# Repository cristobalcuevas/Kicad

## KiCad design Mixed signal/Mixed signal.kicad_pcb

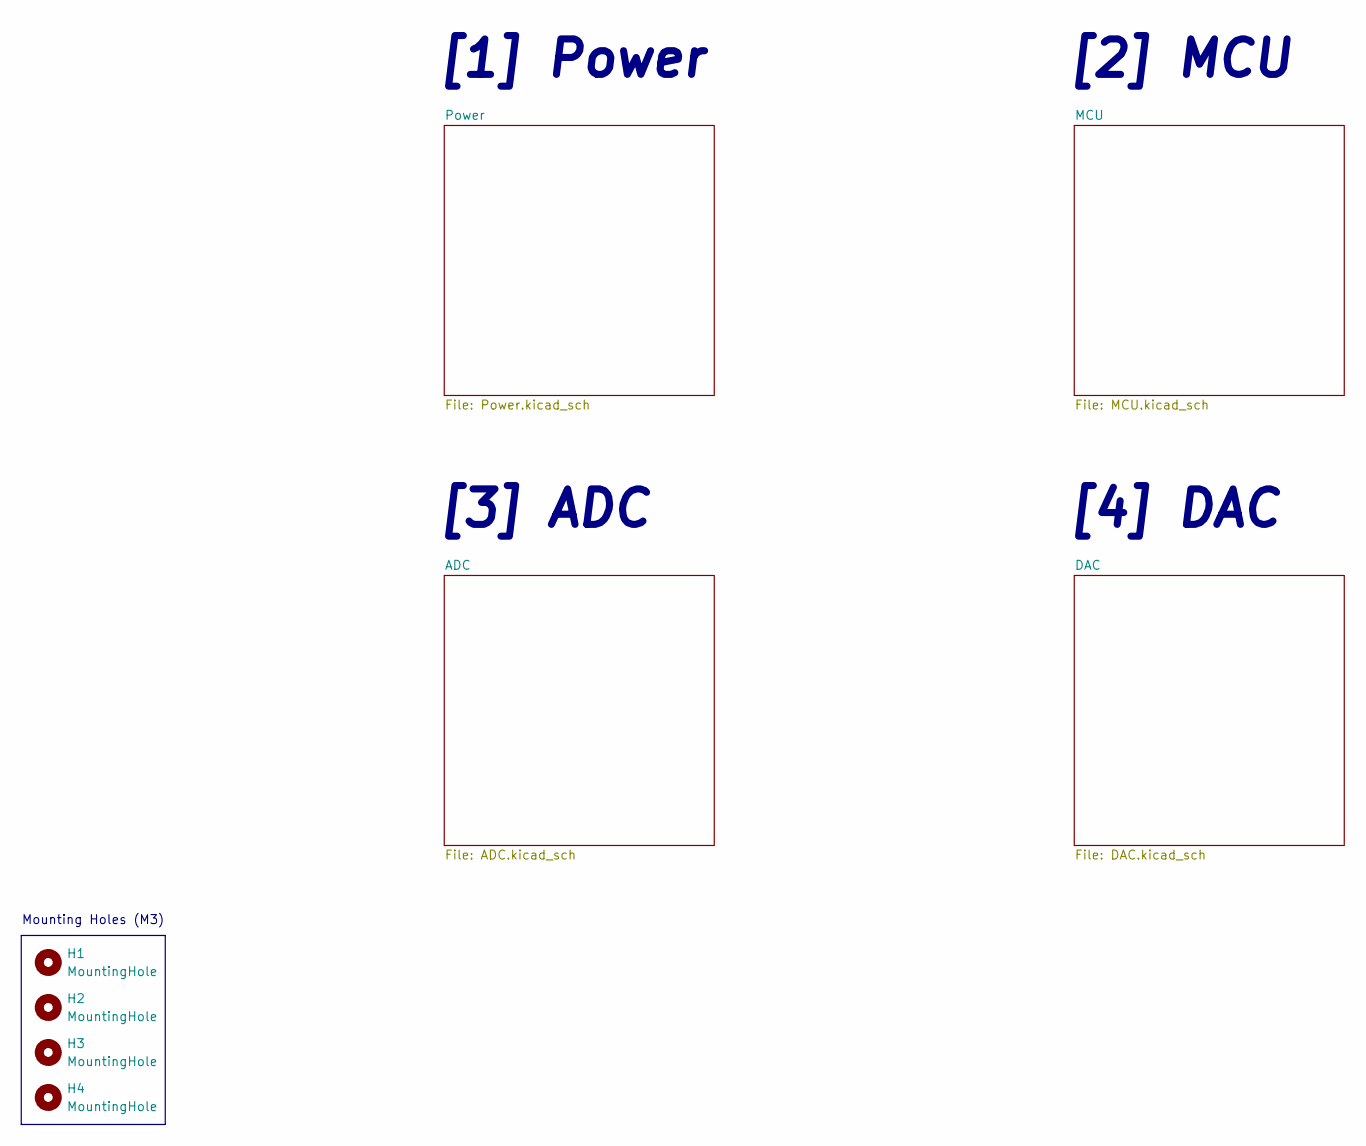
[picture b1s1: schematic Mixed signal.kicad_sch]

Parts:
H1, H2, H3, H4: MountingHole; MountingHole_3.2mm_M3

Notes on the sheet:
[4] DAC
[3] ADC
Mounting Holes (M3)
[2] MCU
[1] Power

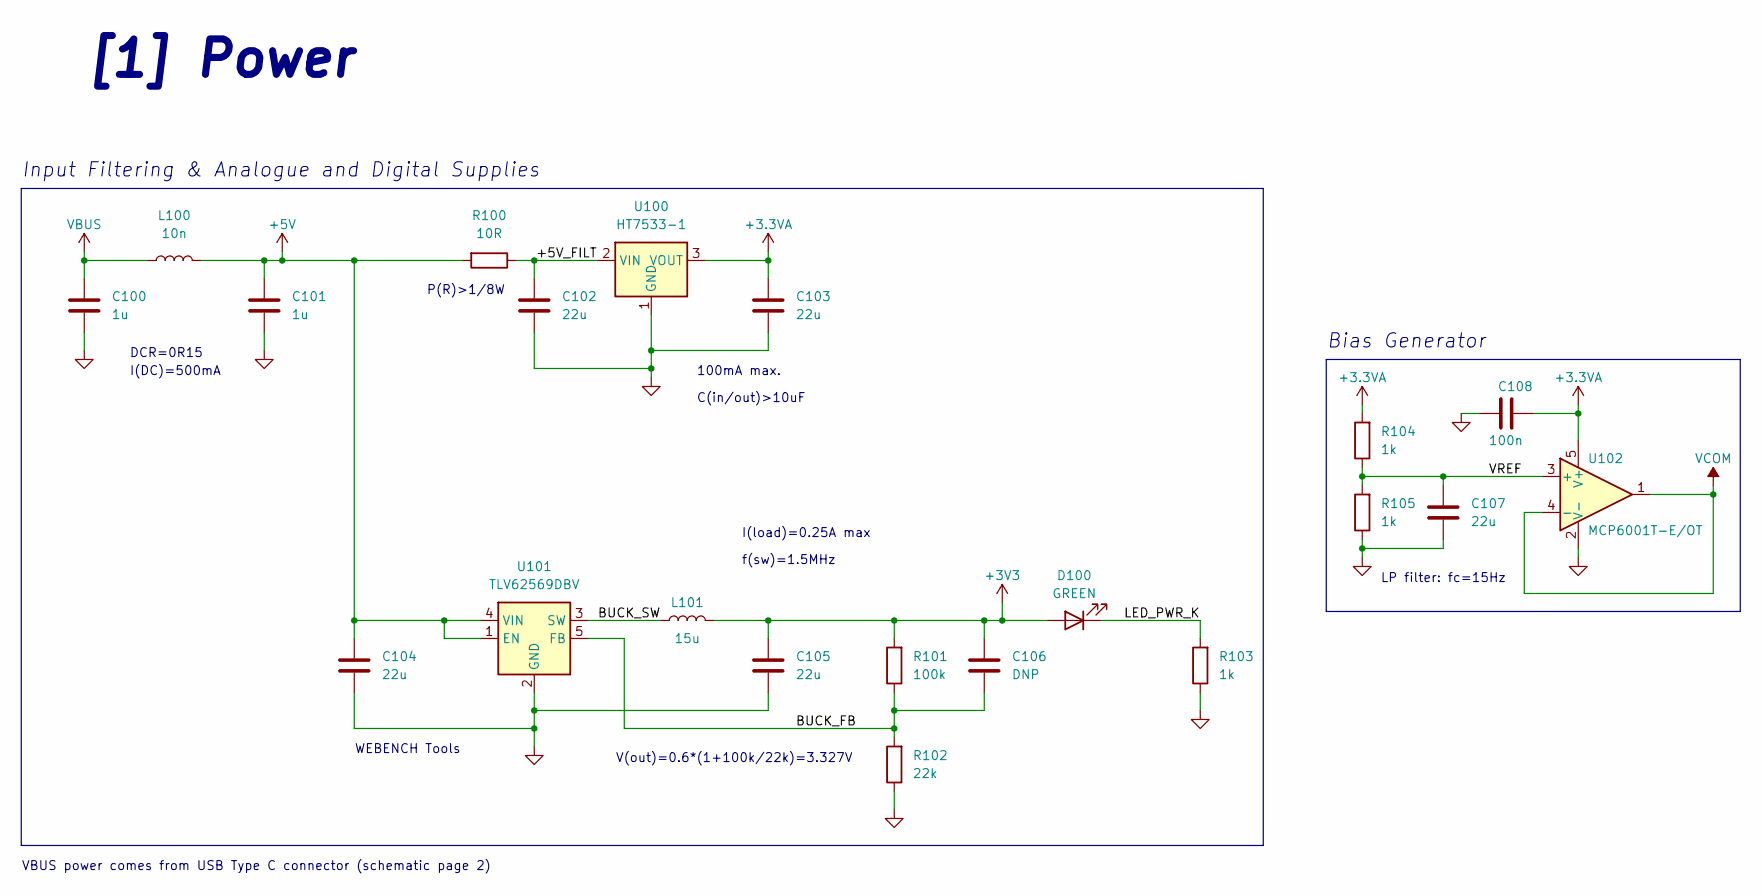
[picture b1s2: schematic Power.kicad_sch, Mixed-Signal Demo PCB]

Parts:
C100, C101: 1u; C_0603_1608Metric
C102, C103, C104, C105, C107: 22u; C_0805_2012Metric
C106: DNP; C_0402_1005Metric
C108: 100n; C_0402_1005Metric
D100: GREEN; LED_0603_1608Metric
L100: 10n; L_0402_1005Metric
L101: 15u; MWSA0603S
R100: 10R; R_0805_2012Metric
R101: 100k; R_0402_1005Metric
R102: 22k; R_0402_1005Metric
R103, R104, R105: 1k; R_0402_1005Metric
U100: HT7533-1; SOT-89-3
U101: TLV62569DBV; SOT-23-5
U102: MCP6001T-E/OT; SOT-23-5

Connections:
+3.3VA: C103.1, C108.1, R104.2, U100.3 (VOUT), U102.5 (V+); also elsewhere on the board
+3V3: C105.1, C106.1, D100.2 (A), L101.2, R101.2; also elsewhere on the board
+5V: C101.1, C104.1, L100.2, R100.2, U101.1 (EN), U101.4 (VIN); also elsewhere on the board
/Power/+5V_FILT: C102.1, R100.1, U100.2 (VIN)
/Power/BUCK_FB: C106.2, R101.1, R102.2, U101.5 (FB)
/Power/BUCK_SW: L101.1, U101.3 (SW)
/Power/LED_PWR_K: D100.1 (K), R103.2
/Power/VREF: C107.1, R104.1, R105.2, U102.3 (+)
GND: C100.2, C101.2, C102.2, C103.2, C104.2, C105.2, C107.2, C108.2, R102.1, R103.1, R105.1, U100.1 (GND), U101.2 (GND), U102.2 (V-); also elsewhere on the board
VBUS: C100.1, L100.1; also elsewhere on the board
VCOM: U102.1, U102.4 (-); also elsewhere on the board

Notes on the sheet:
DCR=0R15
C(in/out)>10uF
V(out)=0.6*(1+100k/22k)=3.327V
I(DC)=500mA
Bias Generator
LP filter: fc=15Hz
100mA max.
f(sw)=1.5MHz
VBUS power comes from USB Type C connector (schematic page 2)
P(R)>1/8W
I(load)=0.25A max
Input Filtering & Analogue and Digital Supplies
[1] Power
WEBENCH Tools

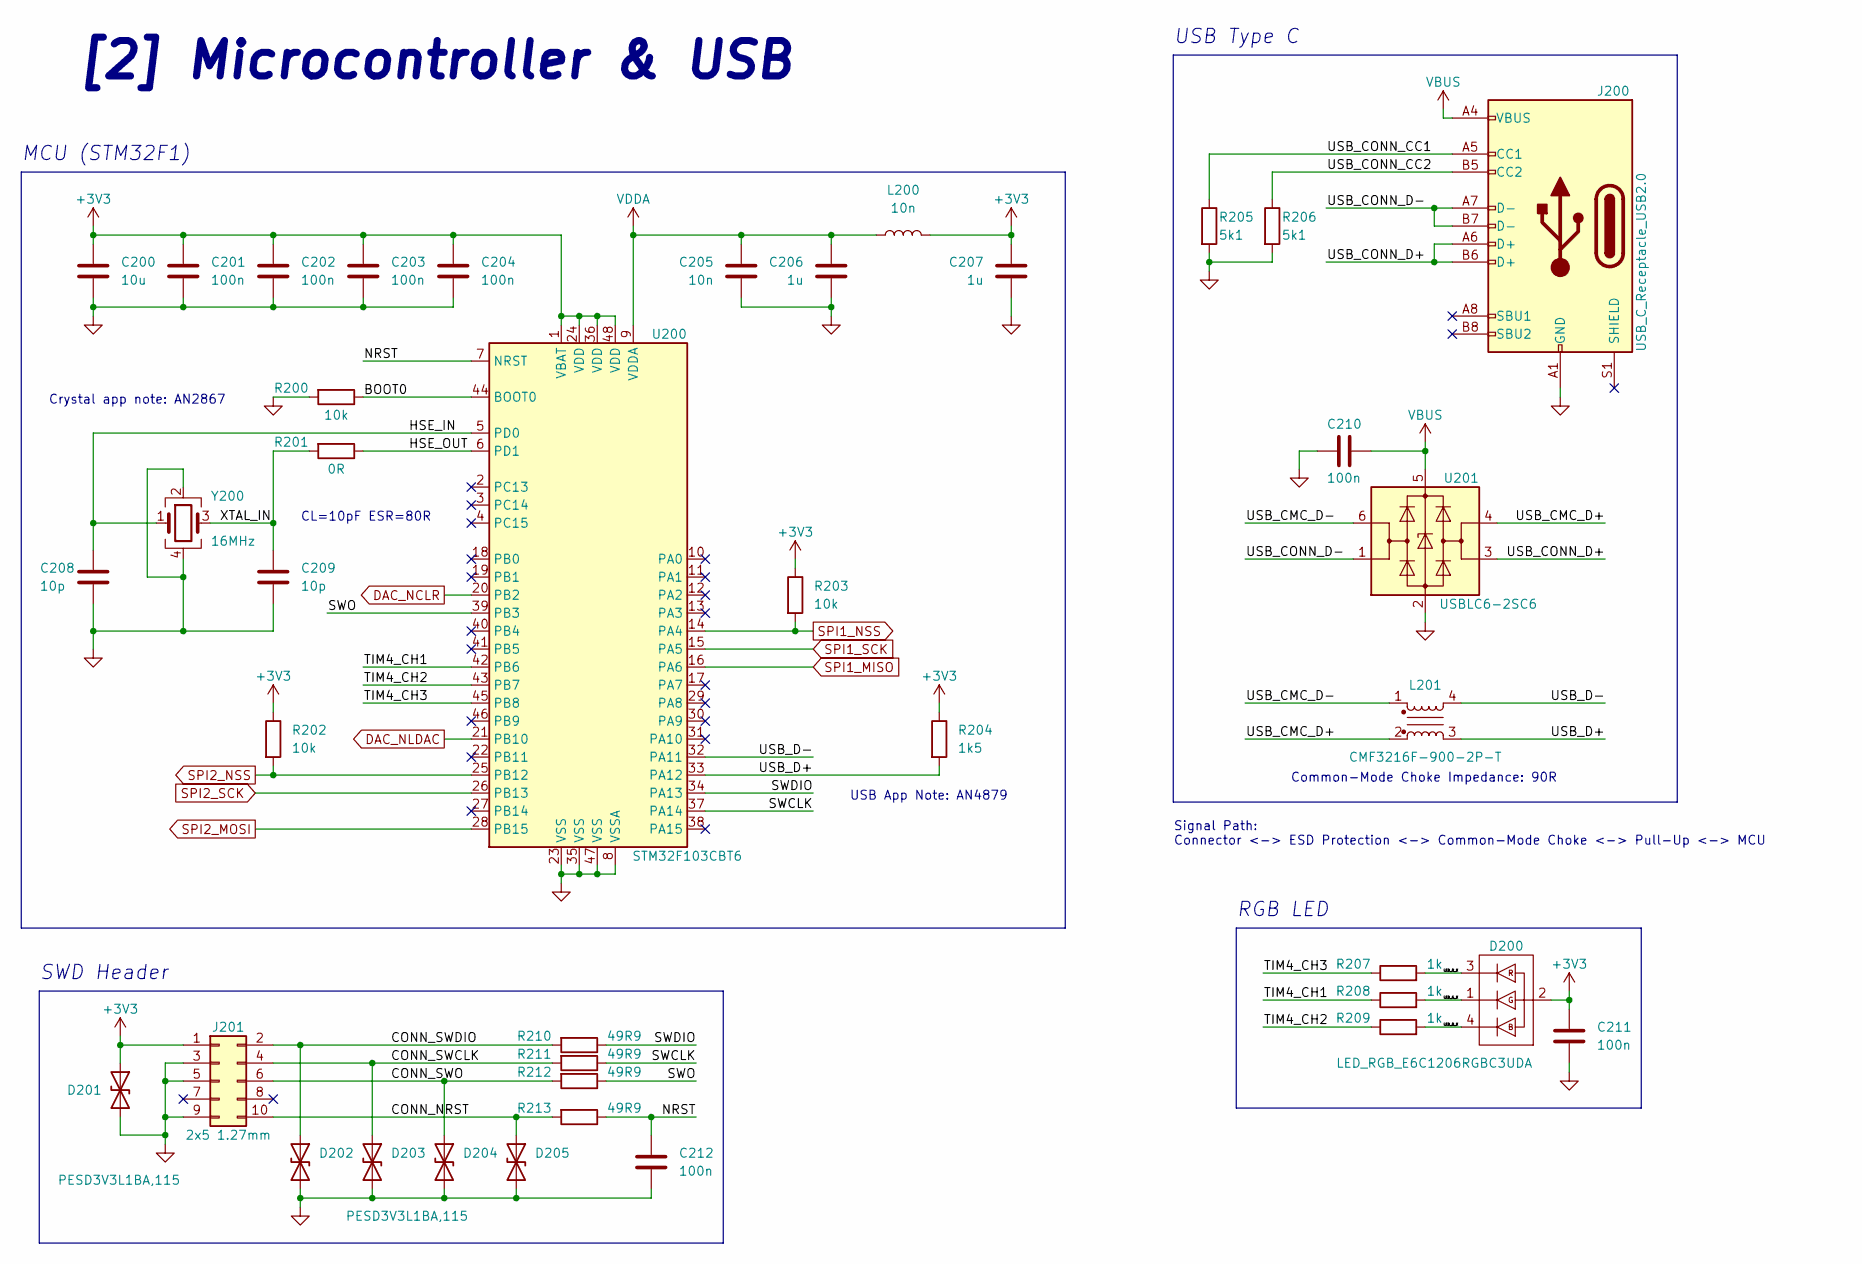
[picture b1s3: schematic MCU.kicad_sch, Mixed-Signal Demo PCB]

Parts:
C200: 10u; C_0603_1608Metric
C201, C202, C203, C204, C210, C211, C212: 100n; C_0402_1005Metric
C205: 10n; C_0402_1005Metric
C206, C207: 1u; C_0603_1608Metric
C208, C209: 10p; C_0402_1005Metric
D200: LED_RGB_E6C1206RGBC3UDA; LED_Cree-PLCC4_2x2mm_CW
D201, D202, D203, D204, D205: PESD3V3L1BA,115; D_SOD-323
J200: USB_C_Receptacle_USB2.0; USB_C_Receptacle_HRO_TYPE-C-31-M-12
J201: 2x5 1.27mm; PinHeader_2x05_P1.27mm_Vertical_SMD
L200: 10n; L_0402_1005Metric
L201: CMF3216F-900-2P-T; CMC-1206
R200, R202, R203: 10k; R_0402_1005Metric
R201: 0R; R_0402_1005Metric
R204: 1k5; R_0402_1005Metric
R205, R206: 5k1; R_0402_1005Metric
R207, R208, R209: 1k; R_0402_1005Metric
R210, R211, R212, R213: 49R9; R_0402_1005Metric
U200: STM32F103CBT6; LQFP-48_7x7mm_P0.5mm; Manufacturer Part Number STM32F103CBT6
U201: USBLC6-2SC6; SOT-23-6
Y200: 16MHz; Crystal_SMD_3225-4Pin_3.2x2.5mm

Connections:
+3V3: C200.1, C201.1, C202.1, C203.1, C204.1, C207.1, C211.1, D200.2, D201.1 (A1), J201.1, L200.2, R202.1, R203.1, R204.1, U200.1 (VBAT), U200.24 (VDD), U200.36 (VDD), U200.48 (VDD); also elsewhere on the board
/MCU/BOOT0: R200.1, U200.44 (BOOT0)
/MCU/CONN_NRST: D205.1 (A1), J201.10, R213.2
/MCU/CONN_SWCLK: D203.1 (A1), J201.4, R211.2
/MCU/CONN_SWDIO: D202.1 (A1), J201.2, R210.2
/MCU/CONN_SWO: D204.1 (A1), J201.6, R212.2
/MCU/HSE_IN: C208.1, U200.5 (PD0), Y200.1
/MCU/HSE_OUT: R201.1, U200.6 (PD1)
/MCU/LED_B_K: D200.4, R209.2
/MCU/LED_G_K: D200.1, R208.2
/MCU/LED_R_K: D200.3, R207.2
/MCU/NRST: C212.1, R213.1, U200.7 (NRST)
/MCU/SWCLK: R211.1, U200.37 (PA14)
/MCU/SWDIO: R210.1, U200.34 (PA13)
/MCU/SWO: R212.1, U200.39 (PB3)
/MCU/TIM4_CH1: R208.1, U200.42 (PB6)
/MCU/TIM4_CH2: R209.1, U200.43 (PB7)
/MCU/TIM4_CH3: R207.1, U200.45 (PB8)
/MCU/USB_CMC_D+: L201.2, U201.4 (I/O2)
/MCU/USB_CMC_D-: L201.1, U201.6 (I/O1)
/MCU/USB_CONN_CC1: J200.A5 (CC1), R205.1
/MCU/USB_CONN_CC2: J200.B5 (CC2), R206.1
/MCU/USB_CONN_D+: J200.A6 (D+), J200.B6 (D+), U201.3 (I/O2)
/MCU/USB_CONN_D-: J200.A7 (D-), J200.B7 (D-), U201.1 (I/O1)
/MCU/USB_D+: L201.3, R204.2, U200.33 (PA12)
/MCU/USB_D-: L201.4, U200.32 (PA11)
/MCU/XTAL_IN: C209.1, R201.2, Y200.3
DAC_NCLR: U200.20 (PB2); also elsewhere on the board
DAC_NLDAC: U200.21 (PB10); also elsewhere on the board
GND: C200.2, C201.2, C202.2, C203.2, C204.2, C205.2, C206.2, C207.2, C208.2, C209.2, C210.2, C211.2, C212.2, D201.2 (A2), D202.2 (A2), D203.2 (A2), D204.2 (A2), D205.2 (A2), J200.A1 (GND), J200.A12 (GND), J200.B1 (GND), J200.B12 (GND), J201.3, J201.5, J201.9, R200.2, R205.2, R206.2, U200.8 (VSSA), U200.23 (VSS), U200.35 (VSS), U200.47 (VSS), U201.2 (GND), Y200.2, Y200.4; also elsewhere on the board
SPI1_MISO: U200.16 (PA6); also elsewhere on the board
SPI1_NSS: R203.2, U200.14 (PA4); also elsewhere on the board
SPI1_SCK: U200.15 (PA5); also elsewhere on the board
SPI2_MOSI: U200.28 (PB15); also elsewhere on the board
SPI2_NSS: R202.2, U200.25 (PB12); also elsewhere on the board
SPI2_SCK: U200.26 (PB13); also elsewhere on the board
VBUS: C210.1, J200.A4 (VBUS), J200.A9 (VBUS), J200.B4 (VBUS), J200.B9 (VBUS), U201.5 (VBUS); also elsewhere on the board
VDDA: C205.1, C206.1, L200.1, U200.9 (VDDA)

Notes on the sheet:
Signal Path: Connector <-> ESD Protection <-> Common-Mode Choke <-> Pull-Up <-> MCU
RGB LED
Crystal app note: AN2867
SWD Header
USB App Note: AN4879
Common-Mode Choke Impedance: 90R
[2] Microcontroller & USB
CL=10pF ESR=80R
MCU (STM32F1)
USB Type C

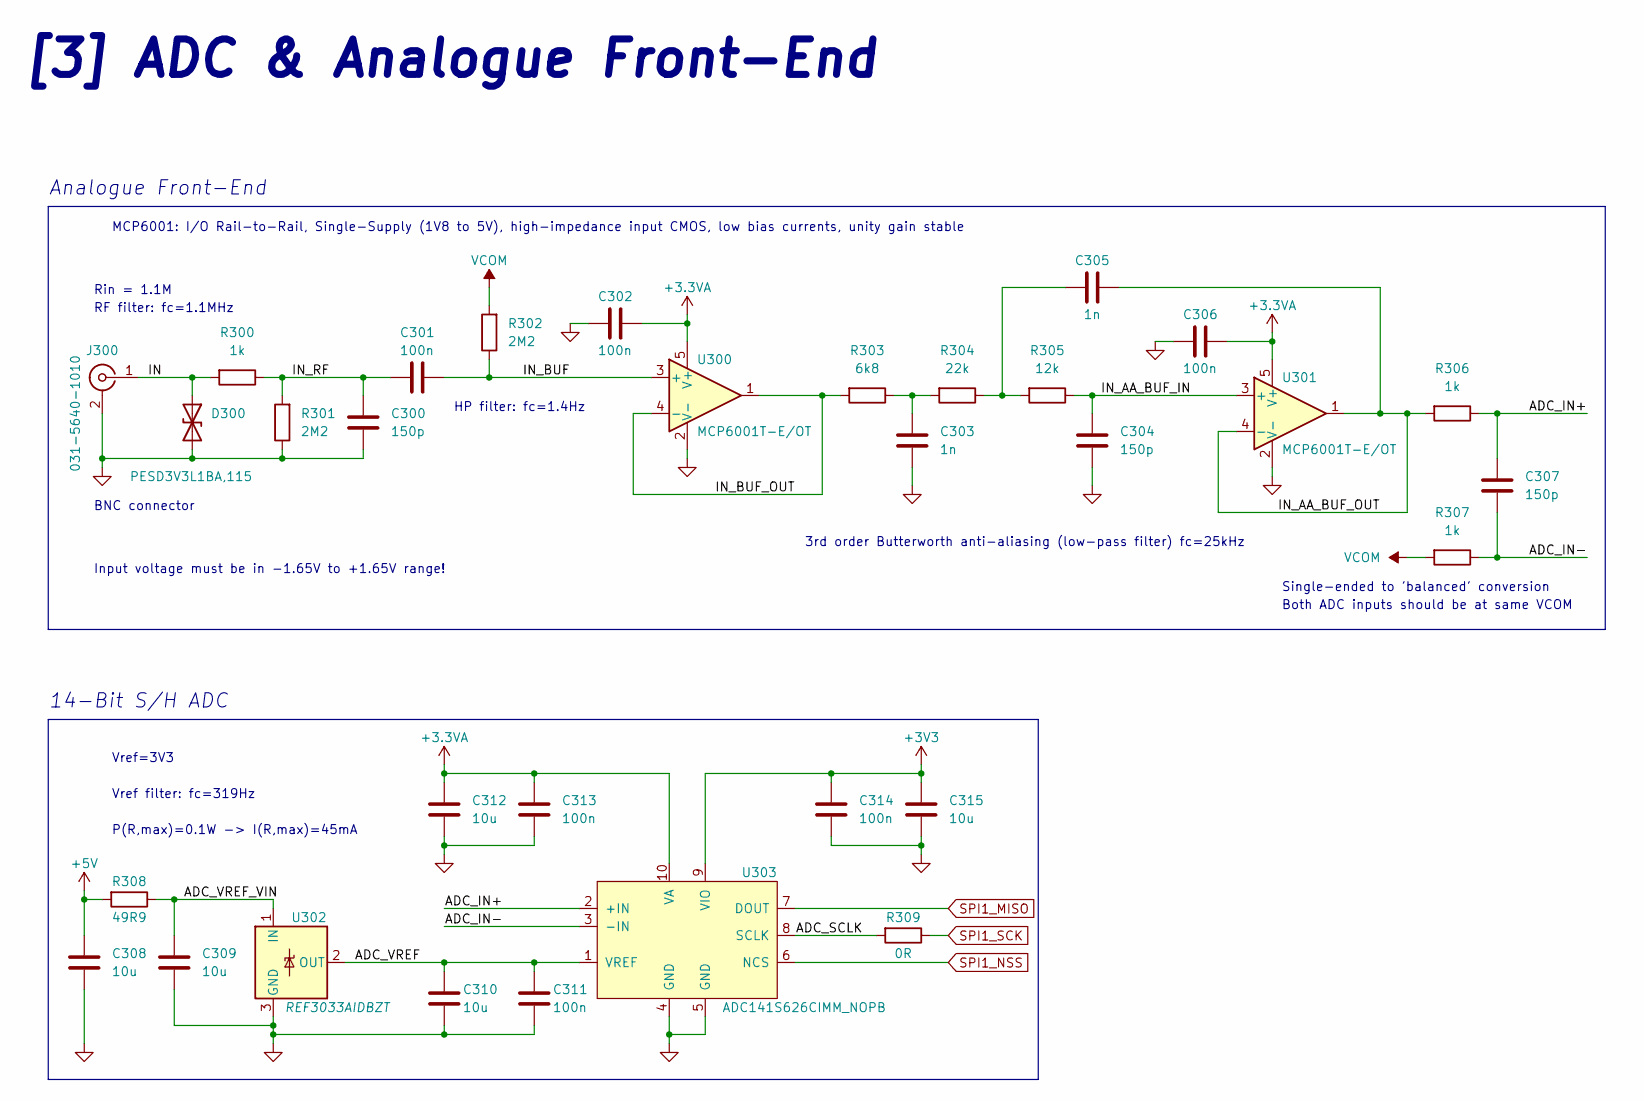
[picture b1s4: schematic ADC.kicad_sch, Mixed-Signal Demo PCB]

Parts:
C300, C304, C307: 150p; C_0402_1005Metric
C301, C302, C306, C311, C313, C314: 100n; C_0402_1005Metric
C303, C305: 1n; C_0402_1005Metric
C308, C309, C310, C312, C315: 10u; C_0603_1608Metric
D300: PESD3V3L1BA,115; D_SOD-323
J300: 031-5640-1010; AMPHENOL-BNC-031-5640-1010
R300, R306, R307: 1k; R_0402_1005Metric
R301, R302: 2M2; R_0402_1005Metric
R303: 6k8; R_0402_1005Metric
R304: 22k; R_0402_1005Metric
R305: 12k; R_0402_1005Metric
R308: 49R9; R_0402_1005Metric
R309: 0R; R_0402_1005Metric
U300, U301: MCP6001T-E/OT; SOT-23-5
U302: REF3033AIDBZT; SOT-23
U303: ADC141S626CIMM_NOPB; VSSOP-10

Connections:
+3.3VA: C302.1, C306.1, C312.1, C313.1, U300.5 (V+), U301.5 (V+), U303.10 (VA); also elsewhere on the board
+3V3: C314.1, C315.1, U303.9 (VIO); also elsewhere on the board
+5V: C308.1, R308.2; also elsewhere on the board
/ADC/ADC_IN+: C307.1, R306.1, U303.2 (+IN)
/ADC/ADC_IN-: C307.2, R307.1, U303.3 (-IN)
/ADC/ADC_SCLK: R309.2, U303.8 (SCLK)
/ADC/ADC_VREF: C310.1, C311.1, U302.2 (OUT), U303.1 (VREF)
/ADC/ADC_VREF_VIN: C309.1, R308.1, U302.1 (IN)
/ADC/IN: D300.1 (A1), J300.1 (In), R300.2
/ADC/IN_AA_BUF_IN: C304.1, R305.1, U301.3 (+)
/ADC/IN_AA_BUF_OUT: C305.2, R306.2, U301.1, U301.4 (-)
/ADC/IN_BUF: C301.1, R302.1, U300.3 (+)
/ADC/IN_BUF_OUT: R303.2, U300.1, U300.4 (-)
/ADC/IN_RF: C300.1, C301.2, R300.1, R301.2
GND: C300.2, C302.2, C303.2, C304.2, C306.2, C308.2, C309.2, C310.2, C311.2, C312.2, C313.2, C314.2, C315.2, D300.2 (A2), J300.2 (Ext), R301.1, U300.2 (V-), U301.2 (V-), U302.3 (GND), U303.4 (GND), U303.5 (GND); also elsewhere on the board
unnamed: C303.1, R303.1, R304.2
unnamed: C305.1, R304.1, R305.2
SPI1_MISO: U303.7 (DOUT); also elsewhere on the board
SPI1_NSS: U303.6 (NCS); also elsewhere on the board
SPI1_SCK: R309.1; also elsewhere on the board
VCOM: R302.2, R307.2; also elsewhere on the board

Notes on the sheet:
HP filter: fc=1.4Hz
Both ADC inputs should be at same VCOM
BNC connector
Rin = 1.1M
14-Bit S/H ADC
Vref filter: fc=319Hz
Input voltage must be in -1.65V to +1.65V range!
Analogue Front-End
Single-ended to 'balanced' conversion
RF filter: fc=1.1MHz
3rd order Butterworth anti-aliasing (low-pass filter) fc=25kHz
MCP6001: I/O Rail-to-Rail, Single-Supply (1V8 to 5V), high-impedance input CMOS, low bias currents, unity gain stable
P(R,max)=0.1W -> I(R,max)=45mA
Vref=3V3
[3] ADC & Analogue Front-End

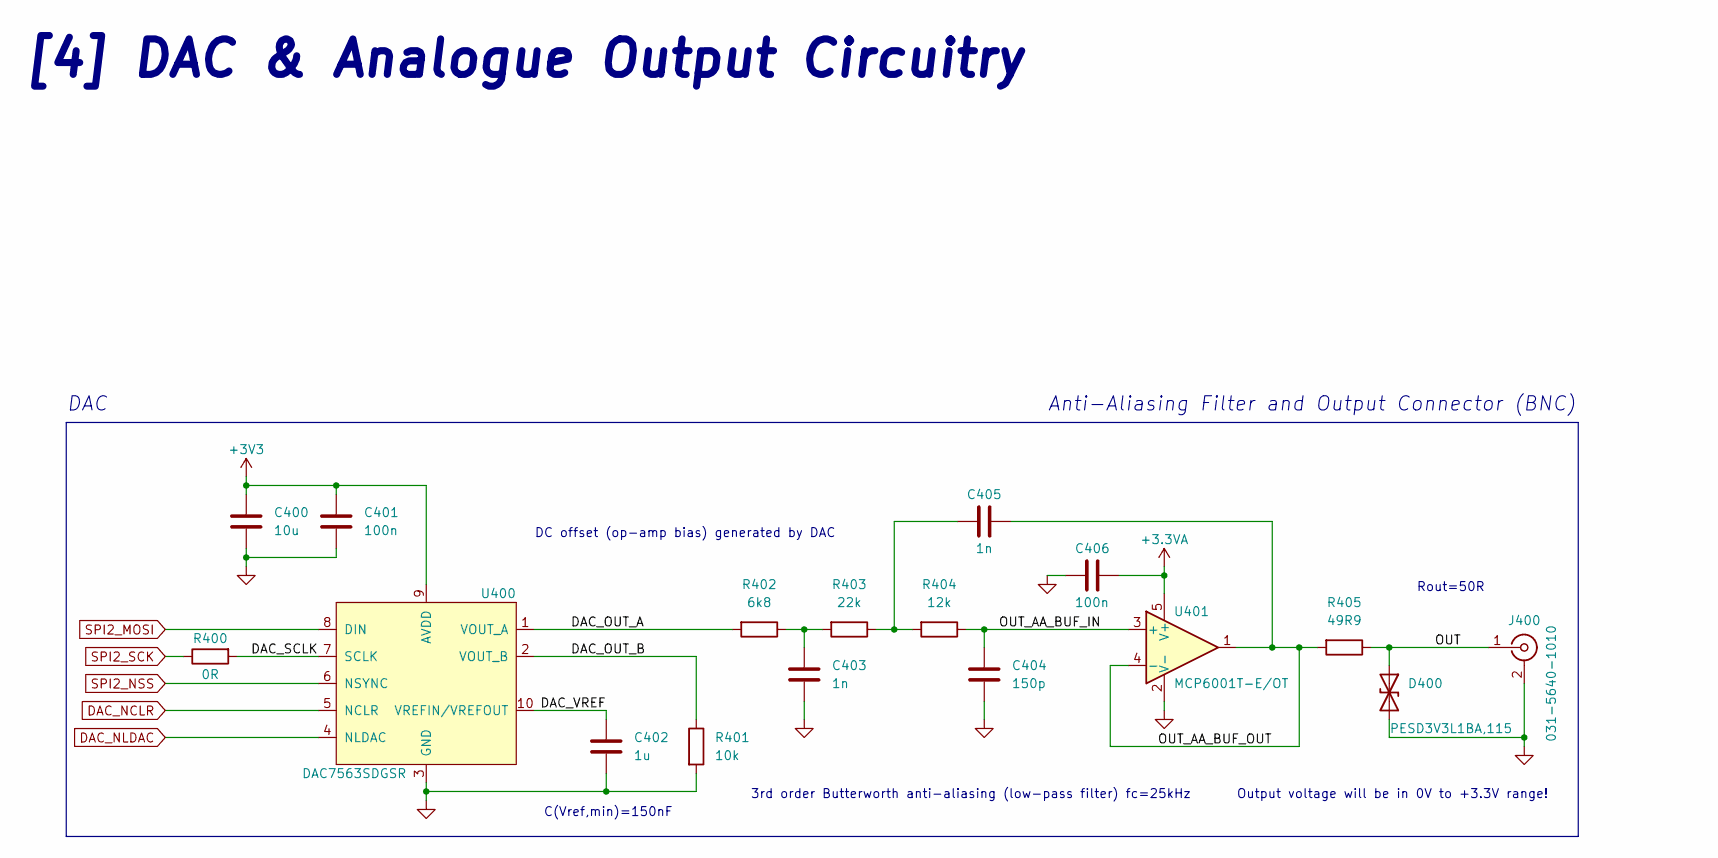
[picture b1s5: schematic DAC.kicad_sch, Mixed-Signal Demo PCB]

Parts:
C400: 10u; C_0603_1608Metric
C401, C406: 100n; C_0402_1005Metric
C402: 1u; C_0603_1608Metric
C403, C405: 1n; C_0402_1005Metric
C404: 150p; C_0402_1005Metric
D400: PESD3V3L1BA,115; D_SOD-323
J400: 031-5640-1010; AMPHENOL-BNC-031-5640-1010
R400: 0R; R_0402_1005Metric
R401: 10k; R_0402_1005Metric
R402: 6k8; R_0402_1005Metric
R403: 22k; R_0402_1005Metric
R404: 12k; R_0402_1005Metric
R405: 49R9; R_0402_1005Metric
U400: DAC7563SDGSR; VSSOP-10
U401: MCP6001T-E/OT; SOT-23-5

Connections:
+3.3VA: C406.1, U401.5 (V+); also elsewhere on the board
+3V3: C400.1, C401.1, U400.9 (AVDD); also elsewhere on the board
/DAC/DAC_OUT_A: R402.2, U400.1 (VOUT_A)
/DAC/DAC_OUT_B: R401.1, U400.2 (VOUT_B)
/DAC/DAC_SCLK: R400.2, U400.7 (SCLK)
/DAC/DAC_VREF: C402.1, U400.10 (VREFIN/VREFOUT)
/DAC/OUT: D400.1 (A1), J400.1 (In), R405.1
/DAC/OUT_AA_BUF_IN: C404.1, R404.1, U401.3 (+)
/DAC/OUT_AA_BUF_OUT: C405.2, R405.2, U401.1, U401.4 (-)
DAC_NCLR: U400.5 (NCLR); also elsewhere on the board
DAC_NLDAC: U400.4 (NLDAC); also elsewhere on the board
GND: C400.2, C401.2, C402.2, C403.2, C404.2, C406.2, D400.2 (A2), J400.2 (Ext), R401.2, U400.3 (GND), U401.2 (V-); also elsewhere on the board
unnamed: C403.1, R402.1, R403.2
unnamed: C405.1, R403.1, R404.2
SPI2_MOSI: U400.8 (DIN); also elsewhere on the board
SPI2_NSS: U400.6 (NSYNC); also elsewhere on the board
SPI2_SCK: R400.1; also elsewhere on the board

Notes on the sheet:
[4] DAC & Analogue Output Circuitry
Anti-Aliasing Filter and Output Connector (BNC)
Rout=50R
Output voltage will be in 0V to +3.3V range!
DAC
C(Vref,min)=150nF
3rd order Butterworth anti-aliasing (low-pass filter) fc=25kHz
DC offset (op-amp bias) generated by DAC

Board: 4 copper layers, 114 parts (0 on the bottom side), 68 nets, no tracks yet.

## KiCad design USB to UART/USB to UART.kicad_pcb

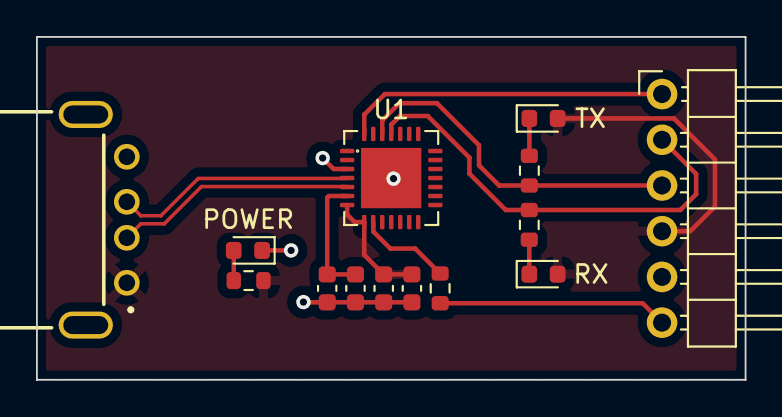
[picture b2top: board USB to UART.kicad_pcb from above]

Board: 2 copper layers, 39.4 x 19.0 mm, 14 parts (0 on the bottom side), 12 nets.

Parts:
C1, C4: 0.1u; C_0603_1608Metric
C2, C3: 4.7u; C_0603_1608Metric
D1: LED_RX; LED_0603_1608Metric
D2: LED_TX; LED_0603_1608Metric
D3: LED_POWER; LED_0603_1608Metric
J1: Connectors; PinHeader_1x06_P2.54mm_Horizontal
J2: USB_A; CONECTOR USB
R1: 1k; R_0603_1608Metric
R2, R3, R4: 220; R_0603_1608Metric
U1: CP2102N-A01-GQFN28; QFN-28-1EP_5x5mm_P0.5mm_EP3.35x3.35mm

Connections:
/CP2102N-GQFN28/3V3: C1.2, C2.1, J1.6, R1.1, U1.6 (VDD)
/CP2102N-GQFN28/D+: J2.3 (D+), U1.4 (D+)
/CP2102N-GQFN28/D-: J2.2 (D-), U1.5 (D-)
/CP2102N-GQFN28/DTR: J1.1, U1.28 (~DTR)
/CP2102N-GQFN28/RX: J1.2, R2.2, U1.25 (RXD)
/CP2102N-GQFN28/TX: J1.3, R3.2, U1.26 (TXD)
/USB/POWER: C3.2, C4.1, D1.2 (A), D2.2 (A), J1.4, J2.1 (VBUS), R4.1, U1.7 (REGIN), U1.8 (VBUS)
GND: C1.1, C2.2, C3.1, C4.2, D3.1 (K), J1.5, J2.4 (GND), J2.5 (Shield), U1.3 (GND), U1.29 (GND)
unnamed: D1.1 (K), R2.1
unnamed: D2.1 (K), R3.1
unnamed: D3.2 (A), R4.2
unnamed: R1.2, U1.9 (~RSTb)

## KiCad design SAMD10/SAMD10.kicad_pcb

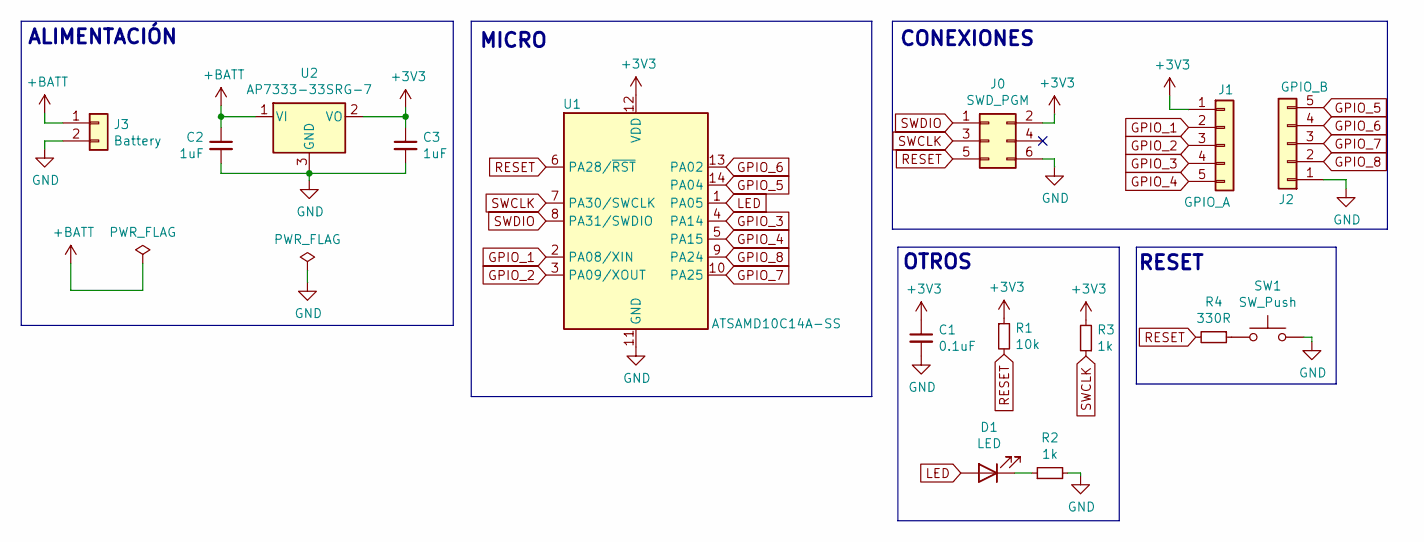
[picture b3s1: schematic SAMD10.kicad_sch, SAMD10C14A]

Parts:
C1: 0.1uF; C_0805_2012Metric
C2, C3: 1uF; C_0805_2012Metric
D1: LED; LED_0805_2012Metric_Pad1.15x1.40mm_HandSolder
J0: SWD_PGM; PinHeader_2x03_P2.54mm_Vertical
J1: GPIO_A; PinHeader_1x05_P2.54mm_Vertical
J2: GPIO_B; PinHeader_1x05_P2.54mm_Vertical
J3: Battery; JST_PH_B2B-PH-K_1x02_P2.00mm_Vertical
R1: 10k; R_0805_2012Metric
R2, R3: 1k; R_0805_2012Metric
R4: 330R; R_0805_2012Metric
SW1: SW_Push; SW_PUSH_6mm
U1: ATSAMD10C14A-SS; SOIC-14_3.9x8.7mm_P1.27mm
U2: AP7333-33SRG-7; SOT-23

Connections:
+3V3: C1.1, C3.1, J0.2, J1.1, R1.1, R3.2, U1.12 (VDD), U2.2 (VO)
+BATT: C2.1, J3.1, U2.1 (VI)
GND: C1.2, C2.2, C3.2, J0.6, J2.1, J3.2, R2.2, SW1.2, U1.11 (GND), U2.3 (GND)
GPIO_1: J1.2, U1.2 (PA08/XIN)
GPIO_2: J1.3, U1.3 (PA09/XOUT)
GPIO_3: J1.4, U1.4 (PA14)
GPIO_4: J1.5, U1.5 (PA15)
GPIO_5: J2.5, U1.14 (PA04)
GPIO_6: J2.4, U1.13 (PA02)
GPIO_7: J2.3, U1.10 (PA25)
GPIO_8: J2.2, U1.9 (PA24)
LED: D1.2 (A), U1.1 (PA05)
unnamed: D1.1 (K), R2.1
unnamed: R4.1, SW1.1
RESET: J0.5, R1.2, R4.2, U1.6 (PA28/~RST)
SWCLK: J0.3, R3.1, U1.7 (PA30/SWCLK)
SWDIO: J0.1, U1.8 (PA31/SWDIO)

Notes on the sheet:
MICRO
OTROS
RESET
ALIMENTACIÓN
CONEXIONES

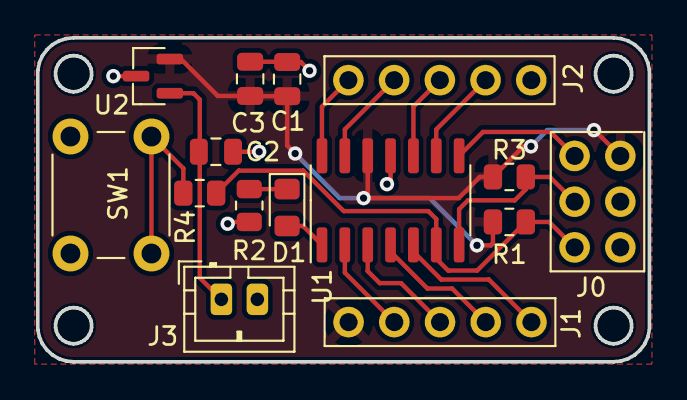
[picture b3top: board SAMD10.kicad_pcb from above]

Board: 2 copper layers, 34.0 x 18.0 mm, 15 parts (0 on the bottom side), 17 nets.

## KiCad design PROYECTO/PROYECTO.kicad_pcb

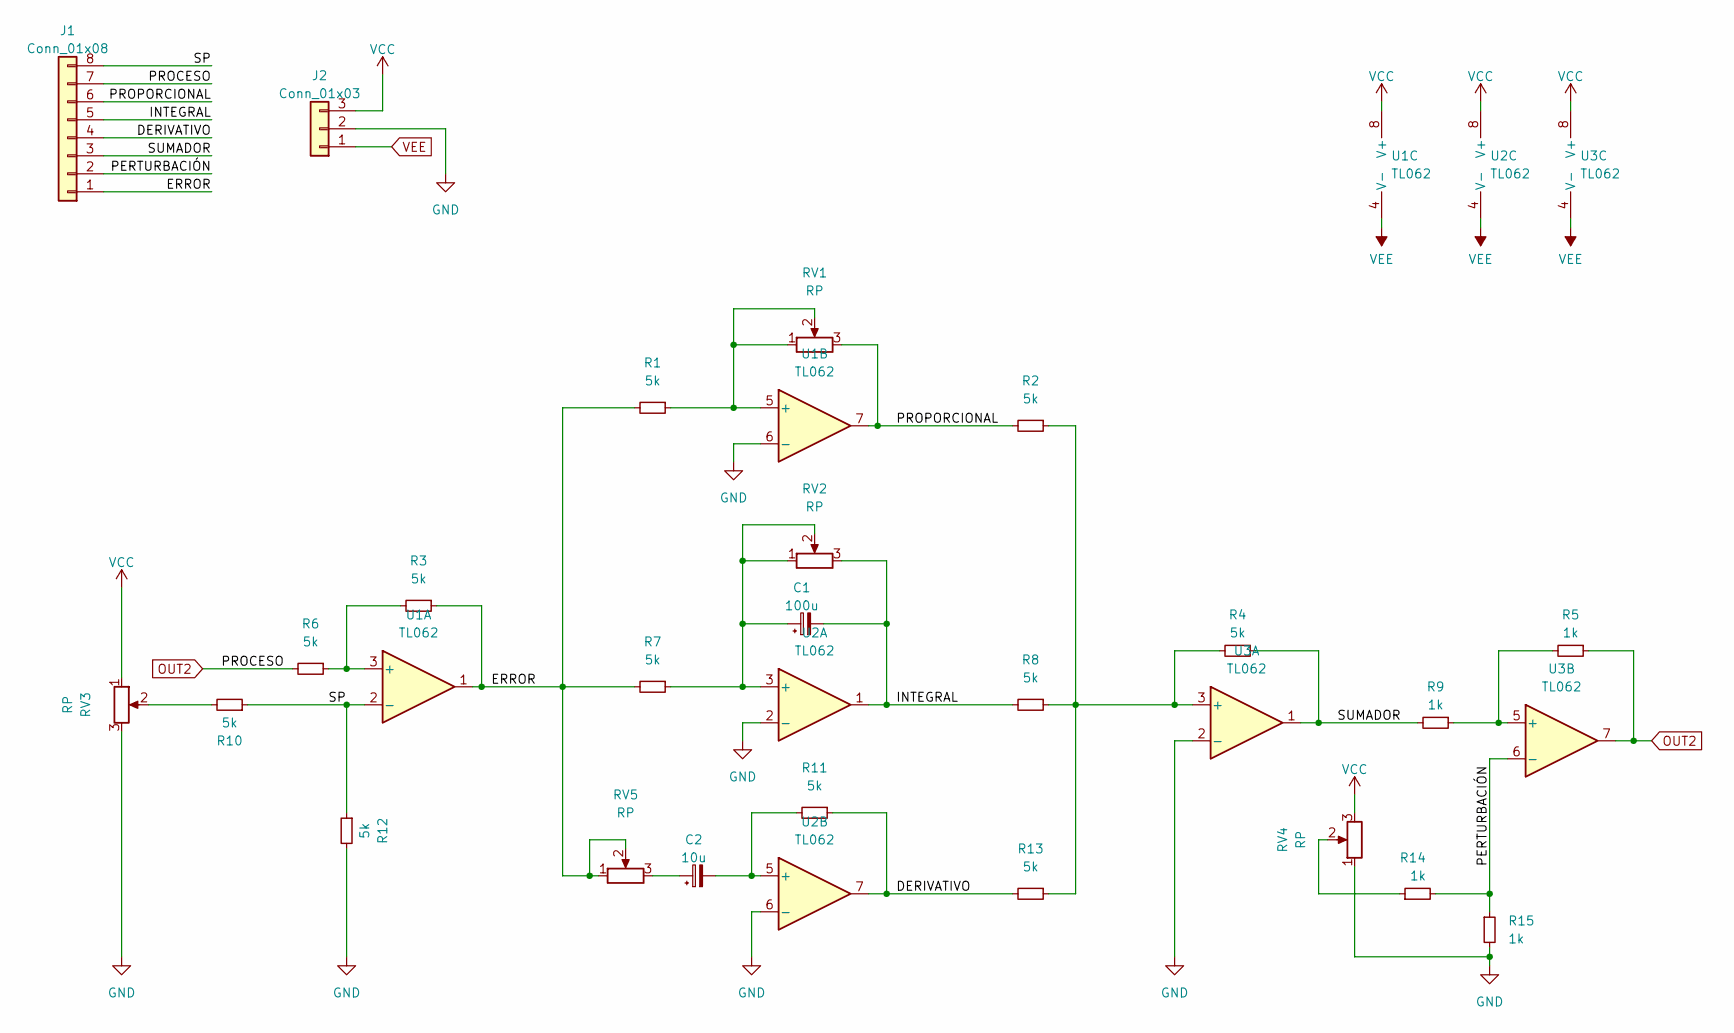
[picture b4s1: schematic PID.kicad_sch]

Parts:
C1: 100u; C_Radial_D5.0mm_H5.0mm_P2.00mm
C2: 10u; C_Radial_D5.0mm_H5.0mm_P2.00mm
J1: Conn_01x08; PinHeader_1x08_P2.54mm_Vertical
J2: Conn_01x03; PinHeader_1x03_P2.54mm_Vertical
R1, R2, R3, R4, R6, R7, R8, R10, R11, R12, R13: 5k; R_Axial_DIN0207_L6.3mm_D2.5mm_P7.62mm_Horizontal
R5, R9, R14, R15: 1k; R_Axial_DIN0207_L6.3mm_D2.5mm_P7.62mm_Horizontal
RV1, RV2, RV3, RV4, RV5: RP; PinHeader_1x03_P2.54mm_Vertical
U1, U2, U3: TL062; DIP-8_W7.62mm

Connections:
/PID/DERIVATIVO: J1.4, R11.1, R13.2, U2.7
/PID/ERROR: J1.1, R1.2, R3.1, R7.2, RV5.1, RV5.2, U1.1
/PID/INTEGRAL: C1.2, J1.5, R8.2, RV2.3, U2.1
/PID/PERTURBACIÓN: J1.2, R14.2, R15.1, U3.6 (-)
/PID/PROPORCIONAL: J1.6, R2.2, RV1.3, U1.7
/PID/SP: J1.8, R10.1, R12.1, U1.2 (-)
/PID/SUMADOR: J1.3, R4.1, R9.2, U3.1
GND: J2.2, R12.2, R15.2, RV3.3, RV4.1, U1.6 (-), U2.2 (-), U2.6 (-), U3.2 (-); also elsewhere on the board
unnamed: C1.1, R7.1, RV2.1, RV2.2, U2.3 (+)
unnamed: C2.1, RV5.3
unnamed: C2.2, R11.2, U2.5 (+)
unnamed: R1.1, RV1.1, RV1.2, U1.5 (+)
unnamed: R3.2, R6.1, U1.3 (+)
unnamed: R5.2, R9.1, U3.5 (+)
unnamed: R10.2, RV3.2
unnamed: R2.1, R4.2, R8.1, R13.1, U3.3 (+)
unnamed: R14.1, RV4.2
OUT2: J1.7, R5.1, R6.2, U3.7
VCC: J2.3, RV3.1, RV4.3, U1.8 (V+), U2.8 (V+), U3.8 (V+); also elsewhere on the board
VEE: J2.1, U1.4 (V-), U2.4 (V-), U3.4 (V-); also elsewhere on the board

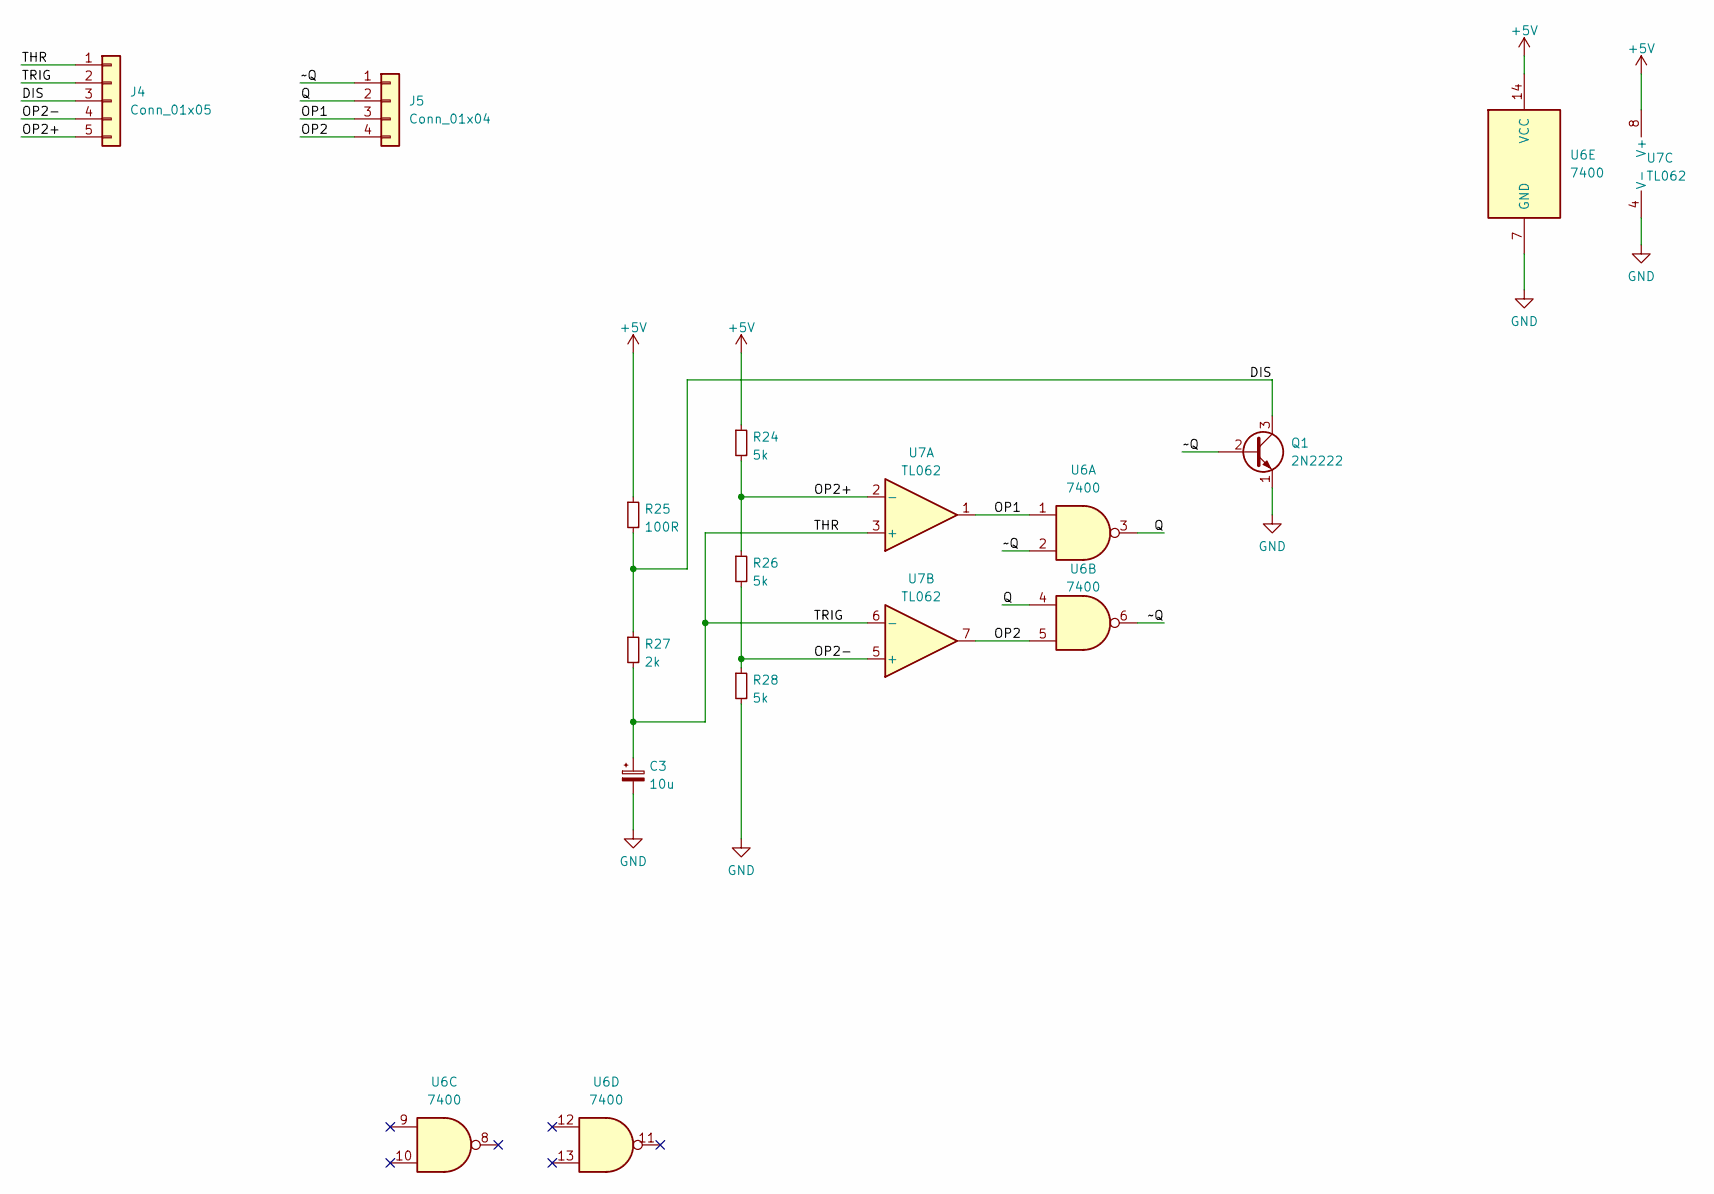
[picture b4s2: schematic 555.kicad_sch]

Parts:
C3: 10u; C_Radial_D5.0mm_H5.0mm_P2.00mm
J4: Conn_01x05; PinHeader_1x05_P2.54mm_Vertical
J5: Conn_01x04; PinHeader_1x04_P2.54mm_Vertical
Q1: 2N2222; TO-92_Inline
R24, R26, R28: 5k; R_Axial_DIN0207_L6.3mm_D2.5mm_P7.62mm_Horizontal
R25: 100R; R_Axial_DIN0207_L6.3mm_D2.5mm_P7.62mm_Horizontal
R27: 2k; R_Axial_DIN0207_L6.3mm_D2.5mm_P7.62mm_Horizontal
U6: 7400; DIP-14_W7.62mm
U7: TL062; DIP-8_W7.62mm

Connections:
+5V: R24.1, R25.1, U6.14 (VCC), U7.8 (V+)
/555/DIS: J4.3, Q1.3 (C), R25.2, R27.1
/555/OP1: J5.3, U6.1, U7.1
/555/OP2: J5.4, U6.5, U7.7
/555/OP2+: J4.5, R24.2, R26.1, U7.2 (-)
/555/OP2-: J4.4, R26.2, R28.1, U7.5 (+)
/555/Q: J5.2, U6.3, U6.4
/555/THR: C3.1, J4.1, J4.2, R27.2, U7.3 (+), U7.6 (-)
/555/~Q: J5.1, Q1.2 (B), U6.2, U6.6
GND: C3.2, Q1.1 (E), R28.2, U6.7 (GND), U7.4 (V-); also elsewhere on the board
